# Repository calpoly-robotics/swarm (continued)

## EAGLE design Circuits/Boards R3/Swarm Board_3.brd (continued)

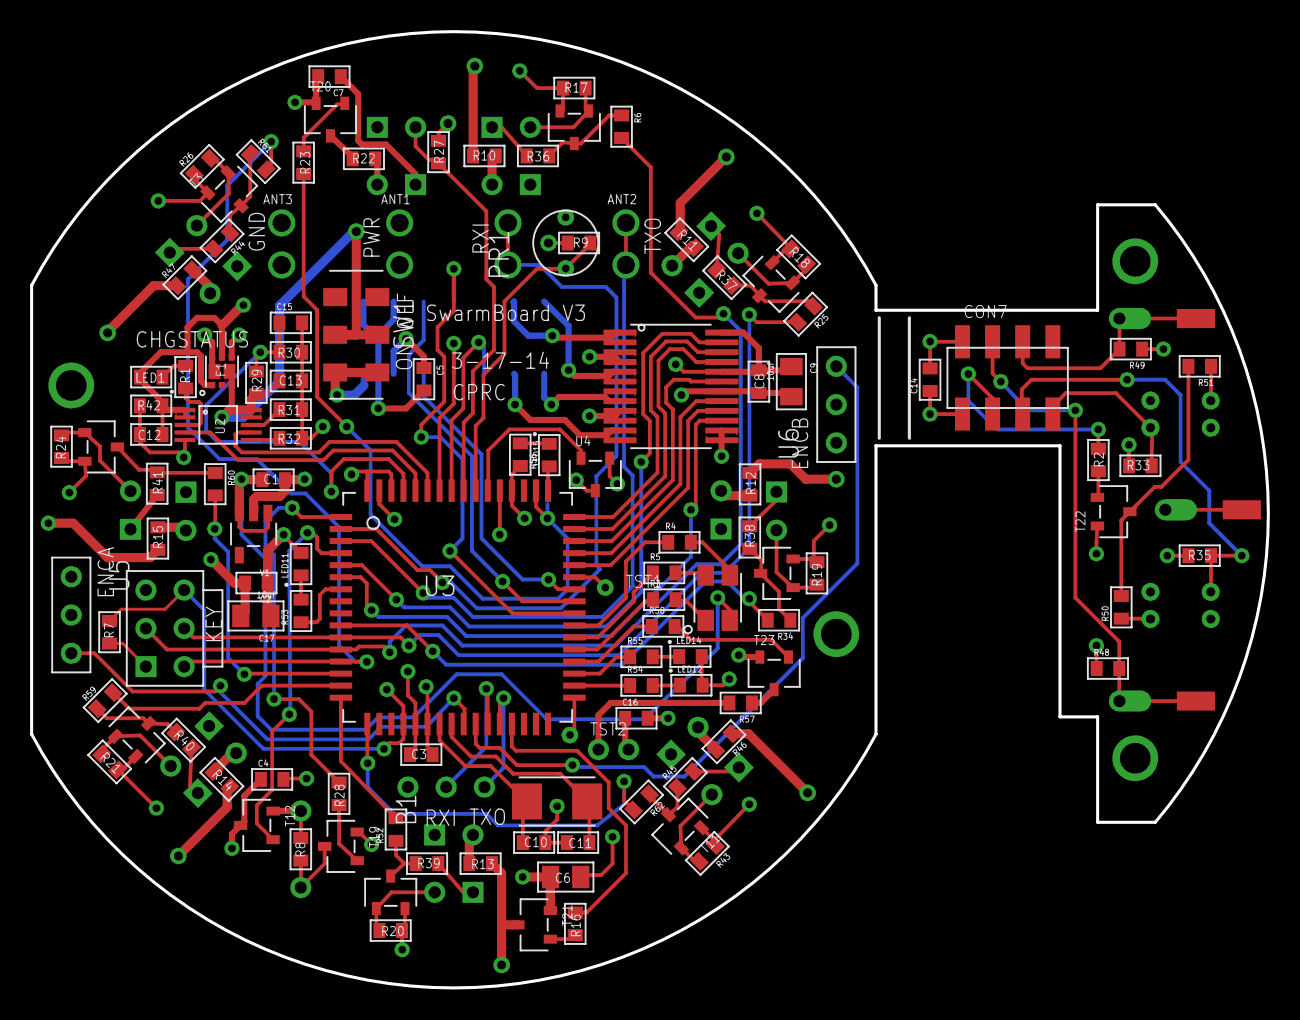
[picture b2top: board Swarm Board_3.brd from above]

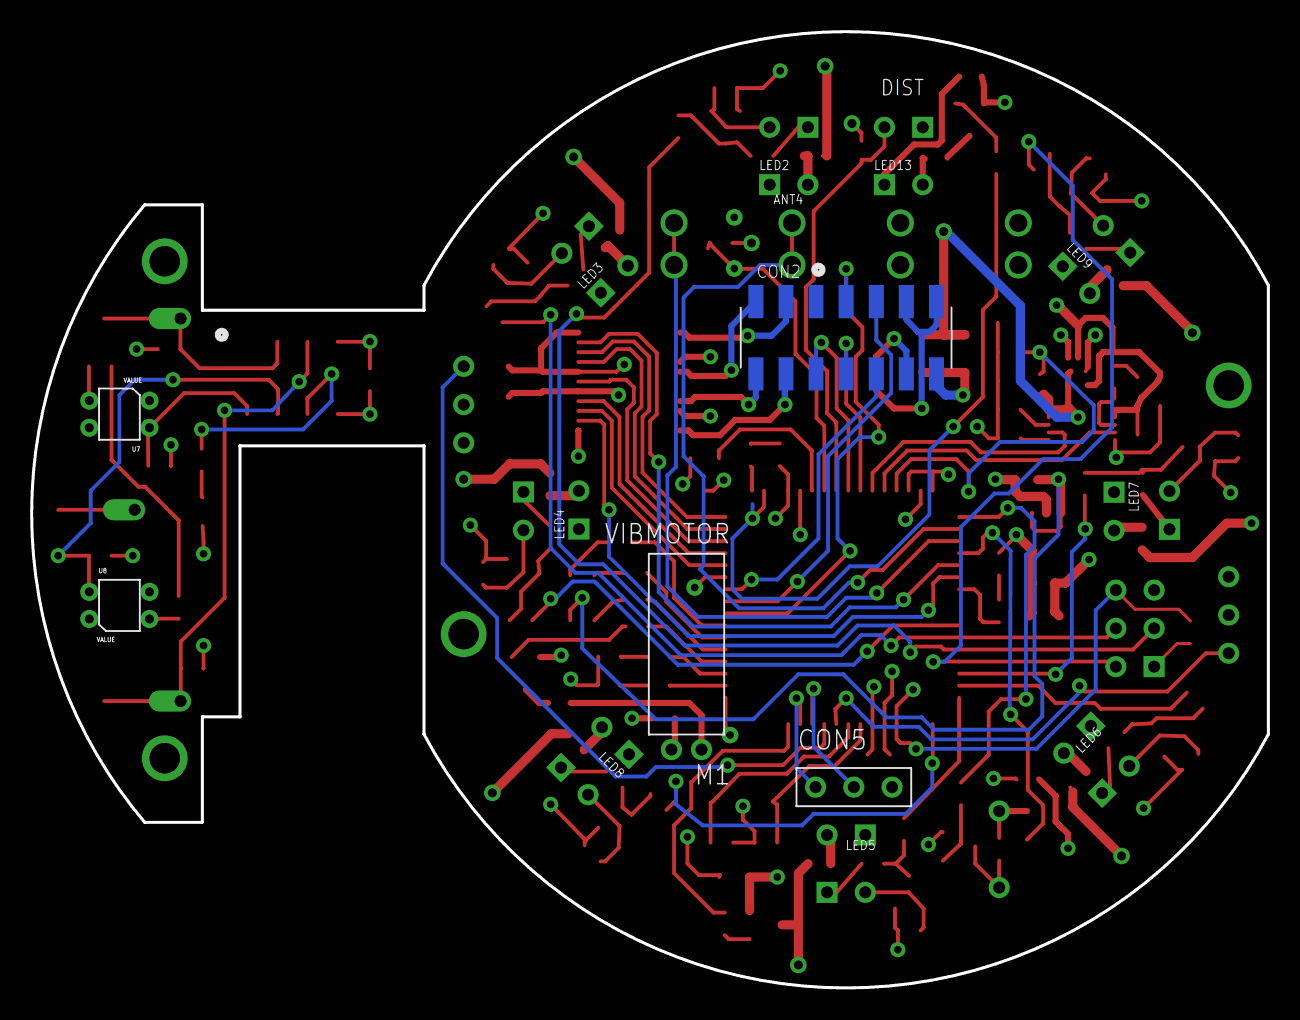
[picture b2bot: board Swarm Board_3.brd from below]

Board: 4 copper layers, 82.1 x 63.5 mm, 149 parts (14 on the bottom side), 116 nets.

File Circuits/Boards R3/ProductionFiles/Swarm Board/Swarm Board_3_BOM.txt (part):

Partlist exported from C:/Users/Jeffrey/Documents/GitHub/swarm/Circuits/Boards R3/Swarm Board_3.sch at 3/21/2014 3:27:04 AM

Qty Value             Device                Package                   Parts                                                                                                      Description                                        
1   0                 RES0603               0603                      R57                                                                                                                                                           
1   1.5k              RES0603               0603                      R1                                                                                                                                                            
8   100               RES0603               0603                      R10, R11, R12, R13, R14, R15, R46, R47                                                                                                                        
2   100k              RES0603               0603                      R29, R30                                                                                                                                                      
22  10k               RES0603               0603                      R6, R7, R17, R18, R19, R20, R21, R24, R25, R26, R27, R31, R34, R42, R43, R48, R49, R52, R59, R60, R61, R62                                                    
3   10uf              CAP0805               0805                      C6, C9, C17                                                                                                                                                   
2   12pf              CAP0603               0603                      C10, C11                                                                                                                                                      
10  1k                RES0603               0603                      R2, R8, R16, R23, R28, R53, R54, R55, R56, R58                                                                                                                
10  1uf               CAP0603               0603                      C1, C2, C3, C4, C5, C7, C8, C14, C15, C16                                                                                                                     
1   20k               RES0603               0603                      R9                                                                                                                                                            
3   220               RES0603               0603                      R3, R50, R51                                                                                                                                                  
2   22k               RES0603               0603                      R33, R35                                                                                                                                                      
1   2k                RES0603               0603                      R32                                                                                                                                                           
1   30                RES0603               0603                      R22                                                                                                                                                           
8   4.7k              RES0603               0603                      R36, R37, R38, R39, R40, R41, R44, R45                                                                                                                        
2   4.7uf             CAP0603               0603                      C12, C13                                                                                                                                                      
1   500k-20k          CDSPHOTORESISTOR      CDSPHOTOCELL              PR1                                                                                                        Digikey Part Number: PDV-P8103-ND                  
2   75                RES0603               0603                      R4, R5                                                                                                                                                        
1   8Mhz              NX5032GA-10.000000MHZ SMDXTAL                   XTAL1                                                                                                      Digikey Part Number: 644-1033-1-ND                 
2   AH182             AH182                 3PINHEADER_.100"          U5, U6                                                                                                     Digikey Part Number: AH182-PL-ADICT-ND             
4   ANTENNA           ANTENNA               ANTENNA                   ANT1, ANT2, ANT3, ANT4                                                                                                                                        
1   ATMEGA1281        ATMEGA1281            TQFP64                    U3                                                                                                         Digikey Part Number: ATMEGA1281V-8AU-ND            
1   CL-SB-22A         CL-SB-22A             CL-SB-22A-01T             SW1                                                                                                        Digikey Part Number: 563-1338-1-ND                 
1   FDFMA2P857        FDFMA2P857            MICROFET2X2MM             F1                                                                                                         Digikey Part Number: FDFMA2P857CT-ND               
2   GREEN             LED0603               LED0603                   LED14, LED15                                                                                                                                                  
1   HEADER_3X1        HEADER_3X1            3PINHEADER_.100"          CON5                                                                                                                                                          
9   IR                LED5MMRA              5MM_LED_RA                LED2, LED3, LED4, LED5, LED6, LED7, LED8, LED9, LED13                                                                                                         
5   IRLML6244TR       IRLML6244TR           SOT23                     T19, T20, T21, T22, T23                                                                                    Digikey Part Number: IRLML6244TRPBFCT-ND           
1   ISP(2X3)          ISP(2X3)              PINHEADER(2X3)            CON1                                                                                                                                                          
1   MAIN_CONNECTOR_14 MAIN_CONNECTOR_14     FEMALE_HEADER_2MM_2X7_SMD CON2                                                                                                       Digikey Part Number: H10965-ND                     
1   MAIN_CONNECTOR_8  MAIN_CONNECTOR_8      FEMALE_HEADER_2MM_2X4     CON7                                                                                                       Digikey Part Number: H10962-ND                     
1   MCP73833          MCP73833              MSOP10                    U2                                                                                                         Manufacturer Part Number: MCP73833-AMI/UN          
1   MCP9700A          MCP9700A              SOT23                     U4                                                                                                         Digikey Part Number: MCP9700AT-E/TTCT-ND           
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
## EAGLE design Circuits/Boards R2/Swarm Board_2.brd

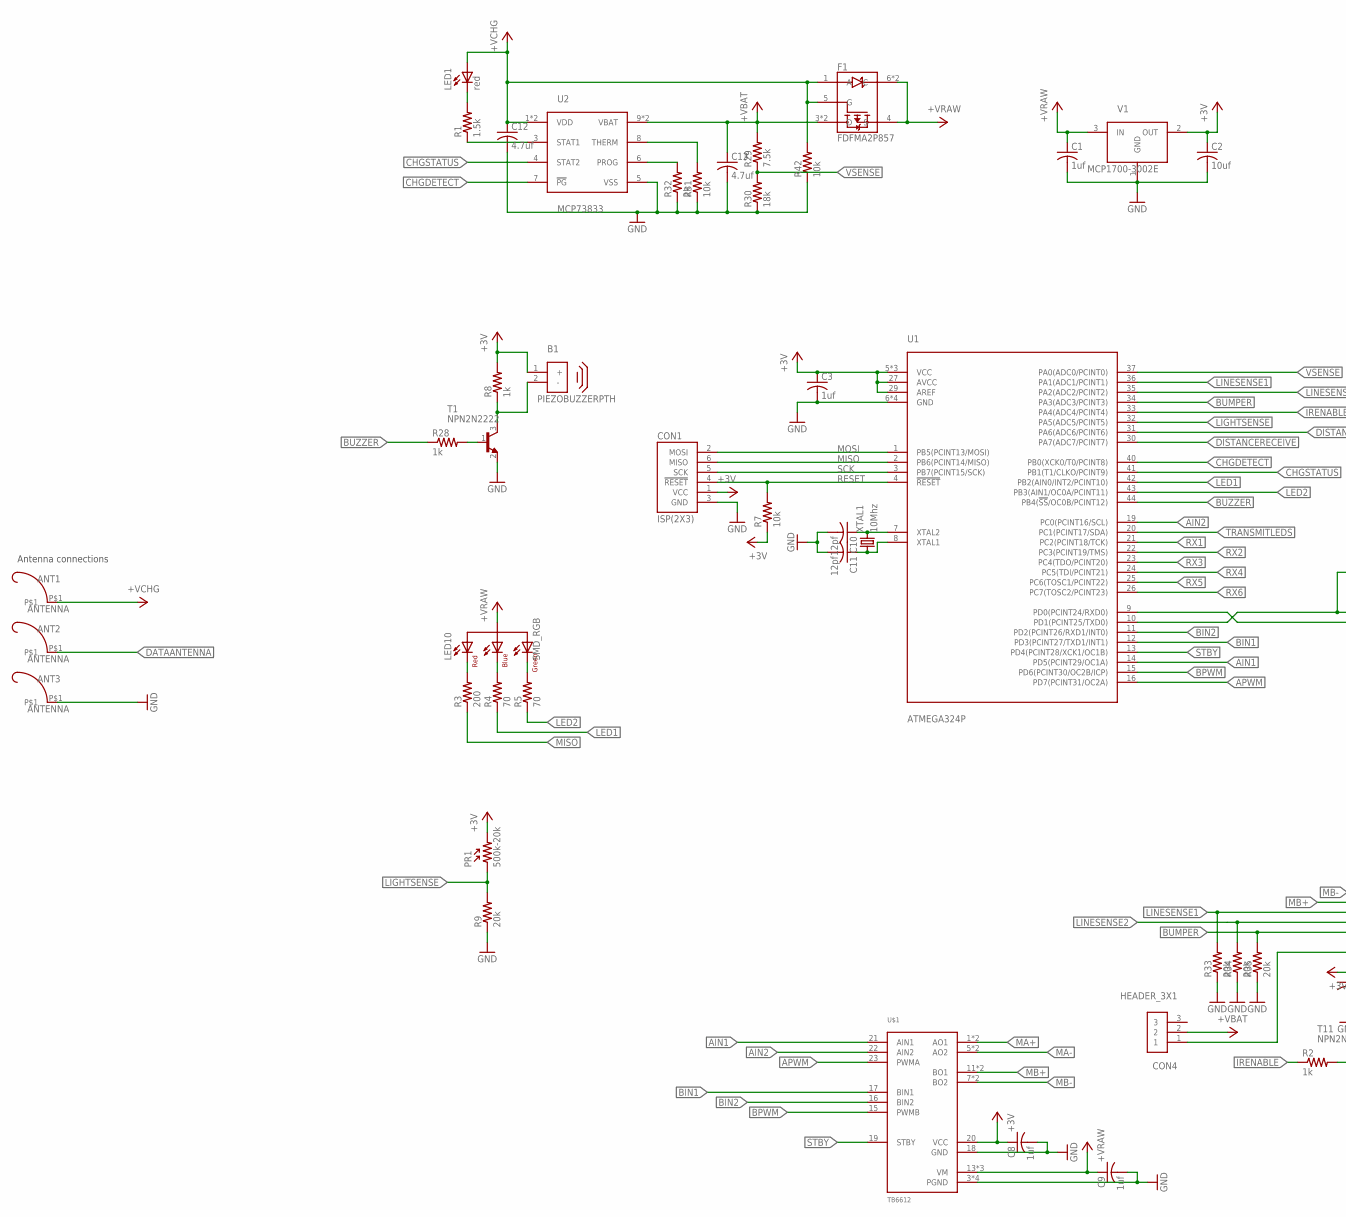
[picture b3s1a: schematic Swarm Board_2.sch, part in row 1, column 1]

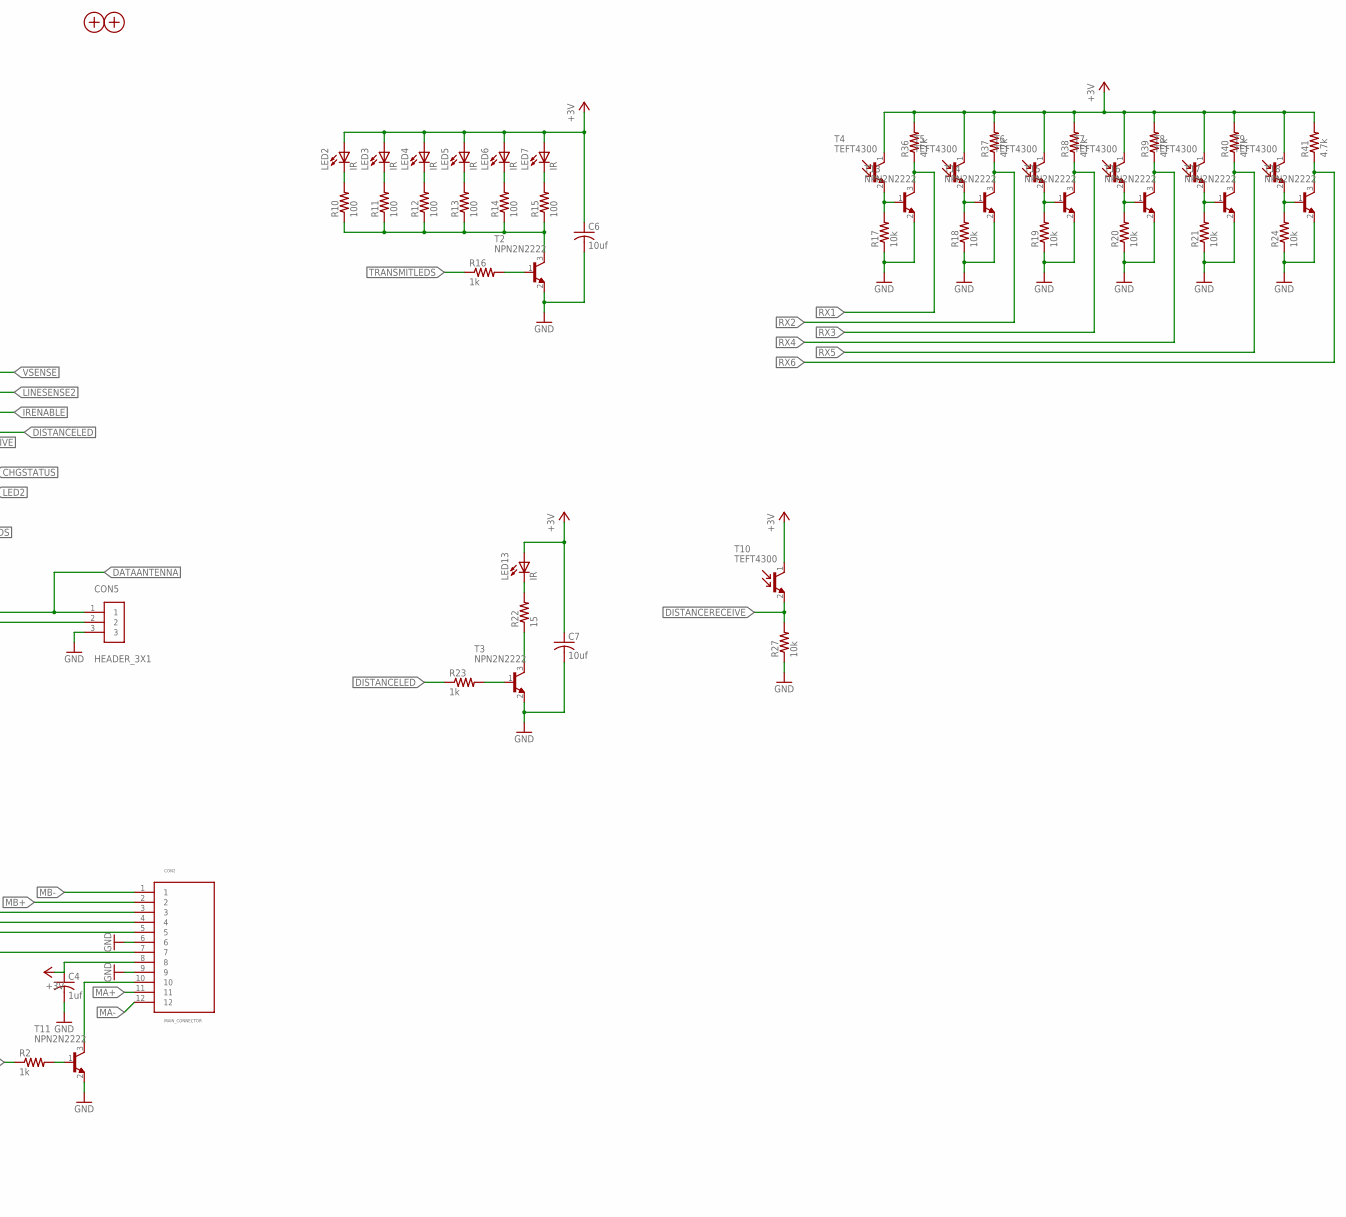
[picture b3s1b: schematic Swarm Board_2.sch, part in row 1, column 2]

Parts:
ANT1, ANT2, ANT3: ANTENNA
B1: PIEZOBUZZERPTH; PIEZOBUZZER
C1, C3, C4, C8, C9: 1uf; 0603
C2, C6, C7: 10uf; 0805
C10, C11: 12pf; 0603
C12, C13: 4.7uf; 0603
CON1: ISP(2X3); PINHEADER(2X3)
CON2: MAIN_CONNECTOR; FEMALE_HEADER_2MM_2X6
CON4, CON5: HEADER_3X1; 3PINHEADER_.100"
F1: FDFMA2P857; MICROFET2X2MM
H1, H2: MOUNTINGHOLE
LED1: red; LED0603
LED2, LED3, LED4, LED5, LED6, LED7, LED13: IR; 5MM_LED_RA
LED10: SMD_RGB; PLCC4
PR1: 500k-20k; CDSPHOTOCELL
R1: 1.5k; 0603
R2, R8, R16, R23, R28: 1k; 0603
R3: 200; 0603
R4, R5: 70; 0603
R7, R17, R18, R19, R20, R21, R24, R27, R31, R42: 10k; 0603
R9, R33, R34, R35: 20k; 0603
R10, R11, R12, R13, R14, R15: 100; 0603
R22: 15; 0603
R29: 7.5k; 0603
R30: 18k; 0603
R32: 2k; 0603
R36, R37, R38, R39, R40, R41: 4.7k; 0603
T1, T2, T3, T11, T13, T14, T15, T16, T17, T18: NPN2N2222; SOT23
T4, T5, T6, T7, T8, T9, T10: TEFT4300; 3MM_LED_RA
U1: ATMEGA324P; TQFP44
U2: MCP73833; MSOP10
U$1: TB6612; 24SSOP
V1: MCP1700-3002E; (TT/NB)SOT-23(3PAD)
XTAL1: 10Mhz; SMDXTAL

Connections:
+3V: B1.1 (+), C2.1, C3.1, C4.1, C6.1, C7.1, C8.1, CON1.1 (VCC), CON2.8, LED2.1 (A), LED3.1 (A), LED4.1 (A), LED5.1 (A), LED6.1 (A), LED7.1 (A), LED13.1 (A), PR1.2, R7.1, R8.2, R36.2, R37.2, R38.2, R39.2, R40.2, R41.2, T4.1 (C), T5.1 (C), T6.1 (C), T7.1 (C), T8.1 (C), T9.1 (C), T10.1 (C), U1.5 (VCC), U1.17 (VCC), U1.27 (AVCC), U1.29 (AREF), U1.38 (VCC), U$1.20 (VCC), V1.2 (OUT)
+VBAT: C13.1, CON4.2, F1.3 (D), F1.8 (D), R29.2, U2.9 (VBAT), U2.10 (VBAT)
+VCHG: ANT1.P$1, C12.1, F1.1 (A), F1.5 (G), LED1.2 (A), R42.2, U2.1 (VDD), U2.2 (VDD)
+VRAW: C1.1, C9.1, F1.4 (S), F1.6 (C), F1.7 (C), LED10.2 (COMMONANODE), U$1.13 (VM), U$1.14 (VM), U$1.24 (VM), V1.3 (IN)
AIN1: U1.14 (PD5(PCINT29/OC1A)), U$1.21 (AIN1)
AIN2: U1.19 (PC0(PCINT16/SCL)), U$1.22 (AIN2)
APWM: U1.16 (PD7(PCINT31/OC2A)), U$1.23 (PWMA)
BIN1: U1.12 (PD3(PCINT27/TXD1/INT1)), U$1.17 (BIN1)
BIN2: U1.11 (PD2(PCINT26/RXD1/INT0)), U$1.16 (BIN2)
BPWM: U1.15 (PD6(PCINT30/OC2B/ICP)), U$1.15 (PWMB)
BUMPER: CON2.5, R35.2, U1.34 (PA3(ADC3/PCINT3))
BUZZER: R28.1, U1.44 (PB4(!SS!/OC0B/PCINT12))
CHGDETECT: U1.40 (PB0(XCK0/T0/PCINT8)), U2.7 (!PG)
CHGSTATUS: U1.41 (PB1(T1/CLKO/PCINT9)), U2.4 (STAT2)
DATAANTENNA: ANT2.P$1, CON5.1, U1.10 (PD1(PCINT25/TXD0))
DISTANCELED: R23.1, U1.31 (PA6(ADC6/PCINT6))
DISTANCERECEIVE: R27.2, T10.2 (E), U1.30 (PA7(ADC7/PCINT7))
GND: ANT3.P$1, C1.2, C2.2, C3.2, C4.2, C6.2, C7.2, C8.2, C9.2, C10.2, C11.2, C12.2, C13.2, CON1.3 (GND), CON2.6, CON2.9, CON5.3, R9.1, R17.1, R18.1, R19.1, R20.1, R21.1, R24.1, R27.1, R30.1, R31.1, R32.1, R33.1, R34.1, R35.1, R42.1, T1.2 (E), T2.2 (E), T3.2 (E), T11.2 (E), T13.2 (E), T14.2 (E), T15.2 (E), T16.2 (E), T17.2 (E), T18.2 (E), U1.6 (GND), U1.18 (GND), U1.28 (GND), U1.39 (GND), U2.5 (VSS), U$1.3 (PGND), U$1.4 (PGND), U$1.9 (PGND), U$1.10 (PGND), U$1.18 (GND), V1.1 (GND)
IRENABLE: R2.1, U1.33 (PA4(ADC4/PCINT4))
LED1: R4.1, U1.42 (PB2(AIN0/INT2/PCINT10))
LED2: R5.1, U1.43 (PB3(AIN1/OC0A/PCINT11))
LIGHTSENSE: PR1.1, R9.2, U1.32 (PA5(ADC5/PCINT5))
LINESENSE1: CON2.3, R33.2, U1.36 (PA1(ADC1/PCINT1))
LINESENSE2: CON2.4, R34.2, U1.35 (PA2(ADC2/PCINT2))
MA+: CON2.11, U$1.1 (AO1), U$1.2 (AO1)
MA-: CON2.12, U$1.5 (AO2), U$1.6 (AO2)
MB+: CON2.2, U$1.11 (BO1), U$1.12 (BO1)
MB-: CON2.1, U$1.7 (BO2), U$1.8 (BO2)
MISO: CON1.6 (MISO), R3.1, U1.2 (PB6(PCINT14/MISO))
MOSI: CON1.2 (MOSI), U1.1 (PB5(PCINT13/MOSI))
unnamed: LED1.1 (C), R1.2
unnamed: R2.2, T11.1 (B)
unnamed: CON2.10, T11.3 (C)
unnamed: CON5.2, U1.9 (PD0(PCINT24/RXD0))
unnamed: B1.2 (-), R8.1, T1.3 (C)
unnamed: R10.1, R11.1, R12.1, R13.1, R14.1, R15.1, T2.3 (C)
unnamed: R16.2, T2.1 (B)
unnamed: R22.1, T3.3 (C)
unnamed: LED2.2 (C), R10.2
unnamed: LED3.2 (C), R11.2
unnamed: LED4.2 (C), R12.2
unnamed: LED5.2 (C), R13.2
unnamed: LED6.2 (C), R14.2
unnamed: LED7.2 (C), R15.2
unnamed: R23.2, T3.1 (B)
unnamed: R31.2, U2.8 (THERM)
unnamed: C10.1, U1.7 (XTAL2), XTAL1.2
unnamed: C11.1, U1.8 (XTAL1), XTAL1.1
unnamed: LED13.2 (C), R22.2
unnamed: R28.2, T1.1 (B)
unnamed: R17.2, T4.2 (E), T13.1 (B)
unnamed: R32.2, U2.6 (PROG)
unnamed: CON2.7, CON4.1
unnamed: LED10.1 (REDCATHODE), R3.2
unnamed: LED10.3 (BLUECATHODE), R4.2
unnamed: LED10.4 (GREENCATHODE), R5.2
unnamed: R1.1, U2.3 (STAT1)
unnamed: R24.2, T9.2 (E), T18.1 (B)
unnamed: R21.2, T8.2 (E), T17.1 (B)
unnamed: R20.2, T7.2 (E), T16.1 (B)
unnamed: R19.2, T6.2 (E), T15.1 (B)
unnamed: R18.2, T5.2 (E), T14.1 (B)
RESET: CON1.4 (!RESET), R7.2, U1.4 (!RESET)
RX1: R36.1, T13.3 (C), U1.21 (PC2(PCINT18/TCK))
RX2: R37.1, T14.3 (C), U1.22 (PC3(PCINT19/TMS))
RX3: R38.1, T15.3 (C), U1.23 (PC4(TDO/PCINT20))
RX4: R39.1, T16.3 (C), U1.24 (PC5(TDI/PCINT21))
RX5: R40.1, T17.3 (C), U1.25 (PC6(TOSC1/PCINT22))
RX6: R41.1, T18.3 (C), U1.26 (PC7(TOSC2/PCINT23))
SCK: CON1.5 (SCK), U1.3 (PB7(PCINT15/SCK))
STBY: U1.13 (PD4(PCINT28/XCK1/OC1B)), U$1.19 (STBY)
TRANSMITLEDS: R16.1, U1.20 (PC1(PCINT17/SDA))
VSENSE: R29.1, R30.2, U1.37 (PA0(ADC0/PCINT0))

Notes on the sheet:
Antenna connections

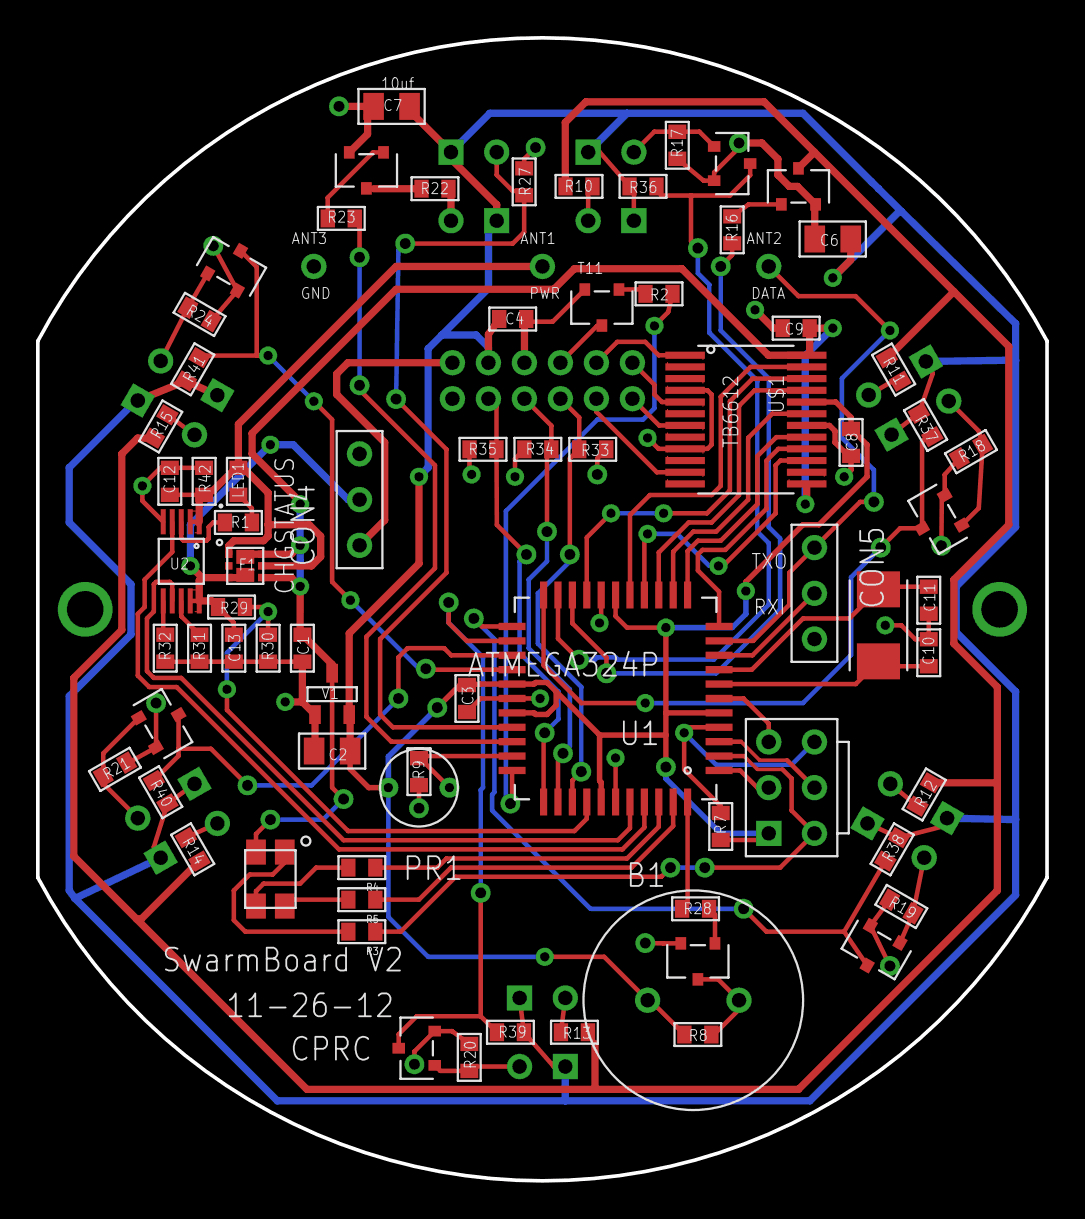
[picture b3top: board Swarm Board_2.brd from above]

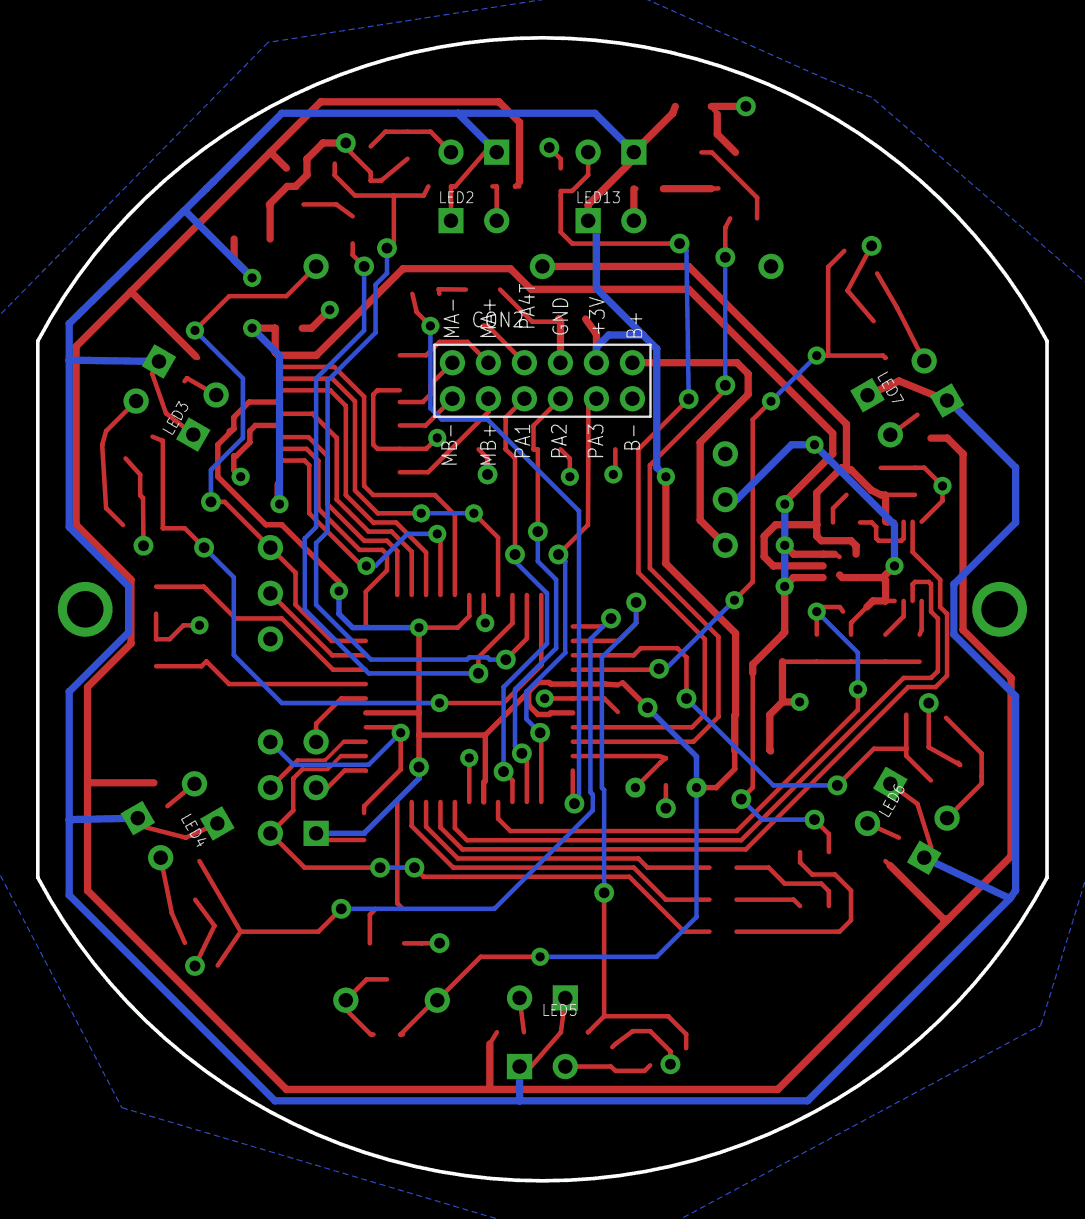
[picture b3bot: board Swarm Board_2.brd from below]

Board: 2 copper layers, 56.1 x 63.5 mm, 94 parts (8 on the bottom side), 73 nets.

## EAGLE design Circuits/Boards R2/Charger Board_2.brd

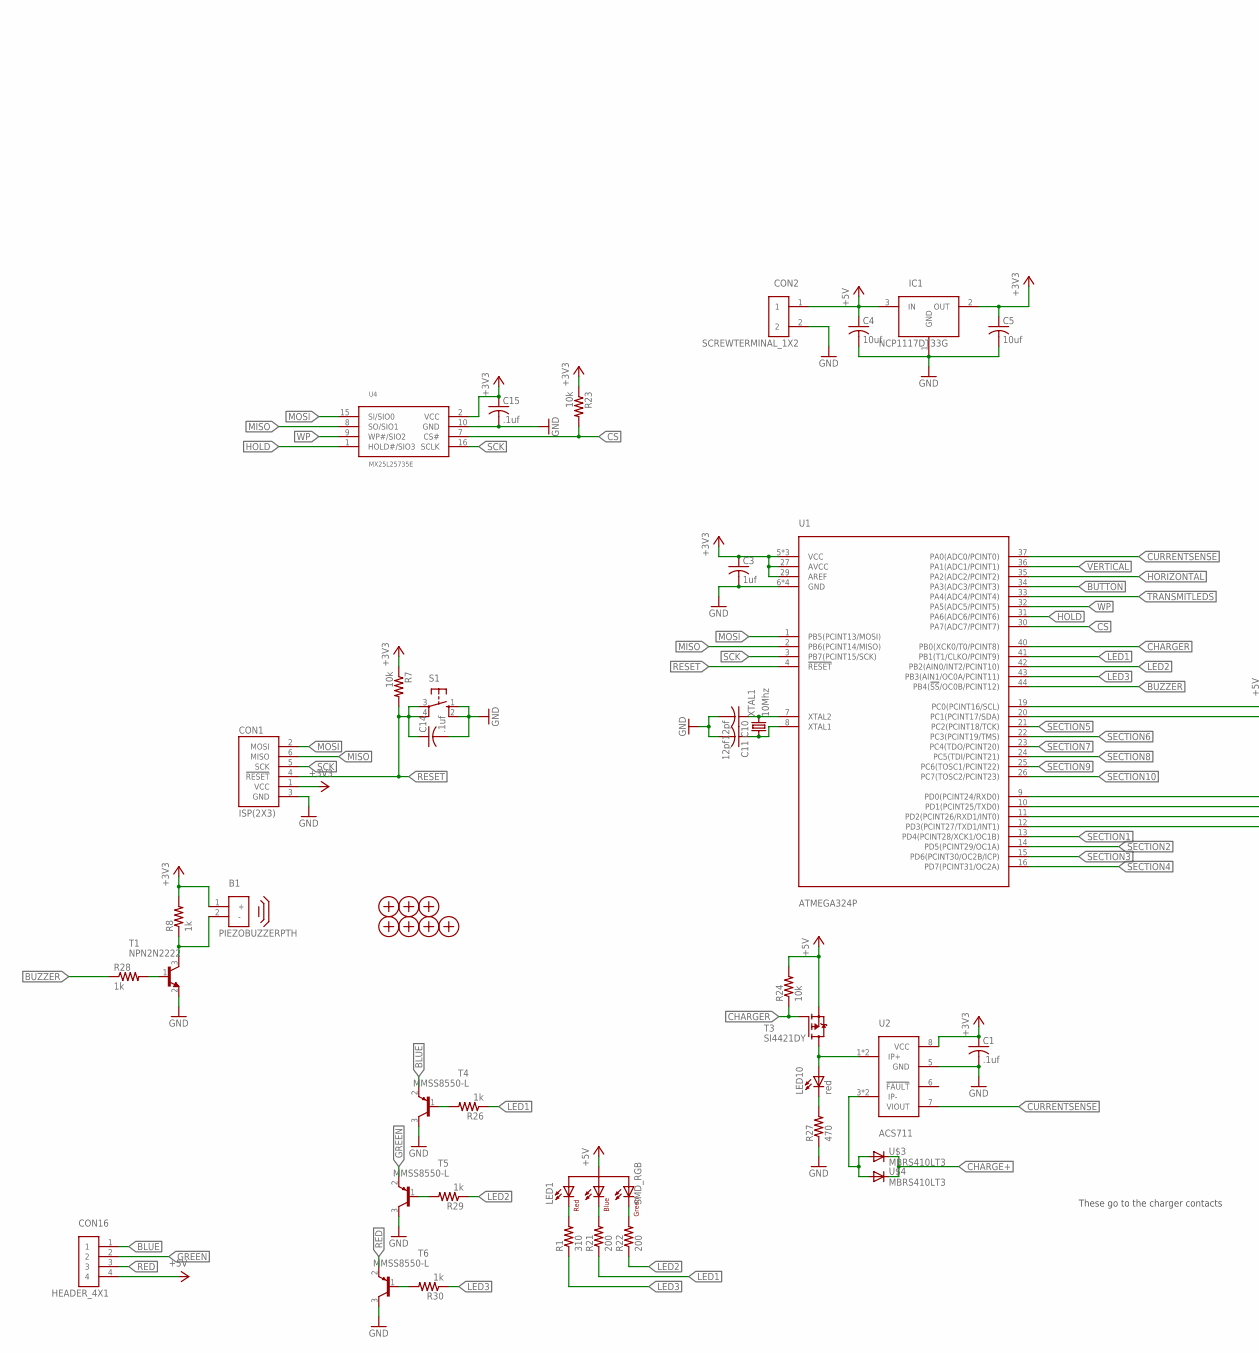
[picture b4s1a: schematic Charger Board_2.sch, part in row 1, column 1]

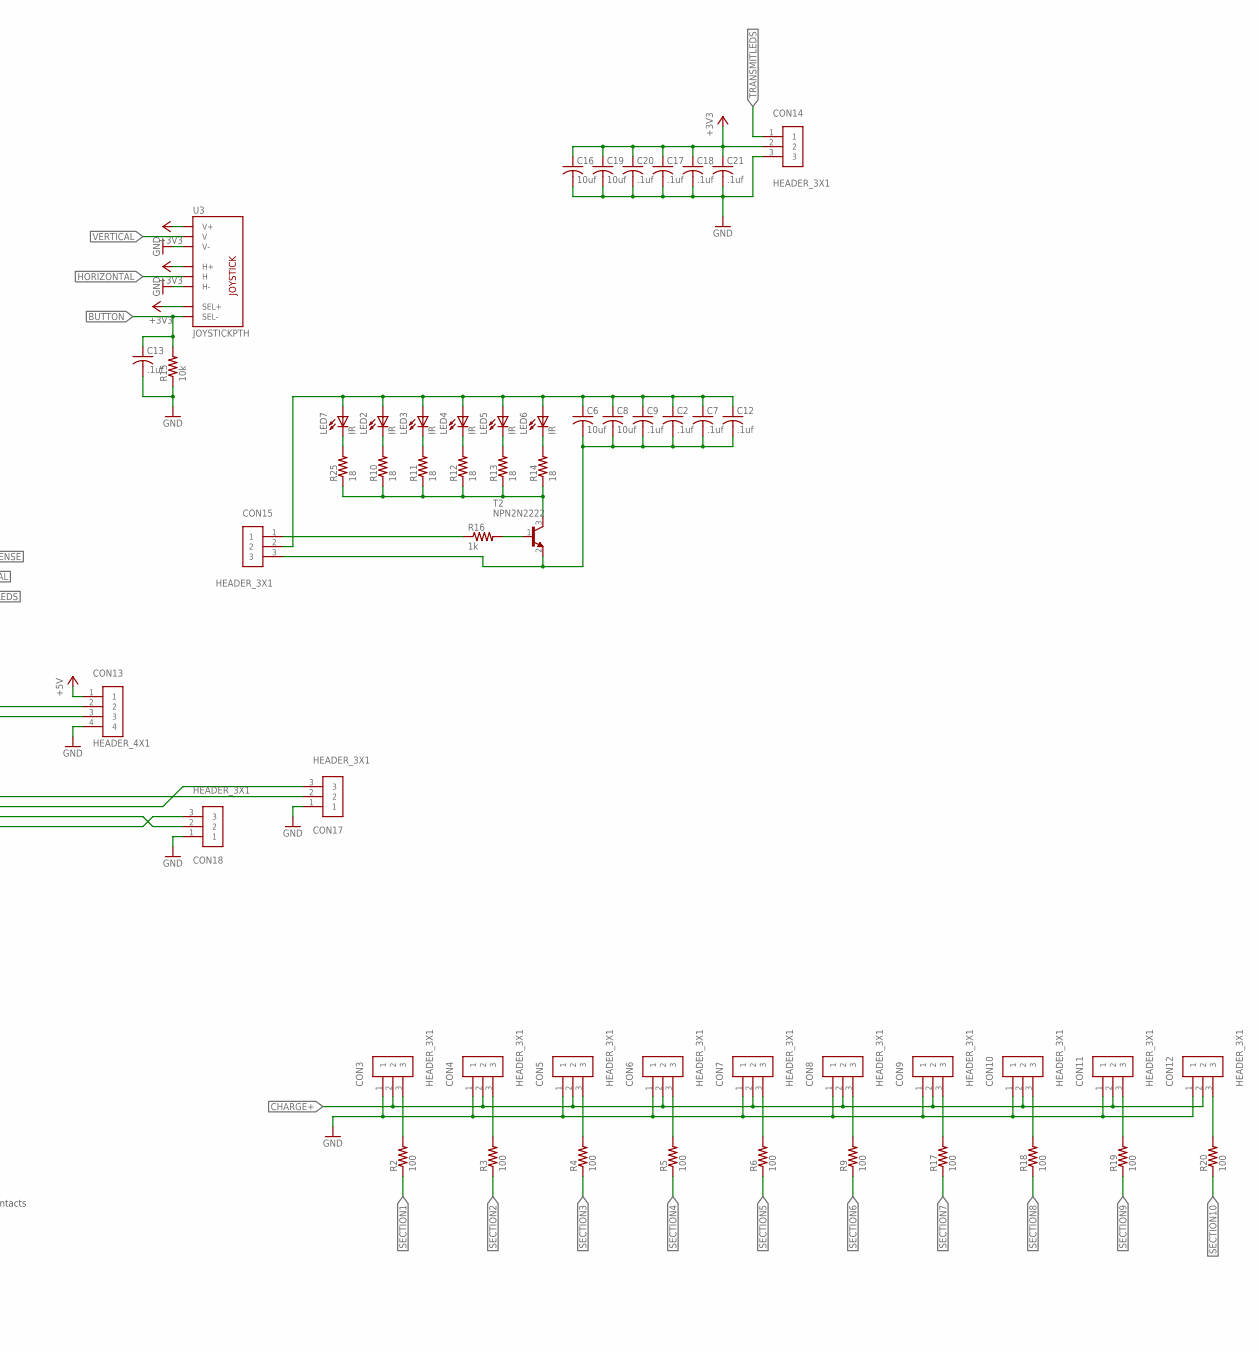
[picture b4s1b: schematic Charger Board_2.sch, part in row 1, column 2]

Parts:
B1: PIEZOBUZZERPTH; PIEZOBUZZER
C1, C2, C7, C9, C12, C13, C14, C15, C17, C18, C20, C21: .1uf; 0603
C3: 1uf; 0603
C4, C5, C6, C8, C16, C19: 10uf; 0805
C10, C11: 12pf; 0603
CON1: ISP(2X3); PINHEADER(2X3)
CON2: SCREWTERMINAL_1X2
CON3, CON4, CON5, CON6, CON7, CON8, CON9, CON10, CON11, CON12, CON14, CON15, CON17, CON18: HEADER_3X1; 3PINHEADER_.100"
CON13, CON16: HEADER_4X1; 4PINHEADER_.100"
H1, H2, H3, H4, H5, H6, H7: MOUNTINGHOLE
IC1: NCP1117DT33G; DPAK
LED1: SMD_RGB; PLCC4
LED2, LED3, LED4, LED5, LED6, LED7: IR; 5MM_LED_RA
LED10: red; LED0603
R1: 310; 0603
R2, R3, R4, R5, R6, R9, R17, R18, R19, R20: 100; 0603
R7, R15, R23, R24: 10k; 0603
R8, R16, R26, R28, R29, R30: 1k; 0603
R10, R11, R12, R13, R14, R25: 18; 0603
R21, R22: 200; 0603
R27: 470; 0603
S1: 10-XX; B3F-10XX
T1, T2: NPN2N2222; SOT23
T3: SI4421DY; S0-8
T4, T5, T6: MMSS8550-L; SOT23
U1: ATMEGA324P; TQFP44
U2: ACS711; 8SOIC
U3: JOYSTICKPTH; JOYSTICK
U4: MX25L25735E; SOIC16R
U$3, U$4: MBRS410LT3; SMD_DIODE
XTAL1: 10Mhz; SMDXTAL

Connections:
+3V3: B1.1 (+), C1.1, C3.1, C5.1, C15.1, C16.1, C17.1, C18.1, C19.1, C20.1, C21.1, CON1.1 (VCC), CON14.2, IC1.2 (OUT), R7.1, R8.2, R23.1, U1.5 (VCC), U1.17 (VCC), U1.27 (AVCC), U1.29 (AREF), U1.38 (VCC), U2.8 (VCC), U3.B1A (SEL+), U3.H1 (H+), U3.V1 (V+), U4.2 (VCC)
+5V: C4.1, CON2.1, CON13.1, CON16.4, IC1.3 (IN), LED1.2 (COMMONANODE), R24.2, T3.1 (S), T3.2 (S), T3.3 (S)
BLUE: CON16.1, T4.2 (E)
BUTTON: C13.1, R15.2, U1.34 (PA3(ADC3/PCINT3)), U3.B2A (SEL-)
BUZZER: R28.1, U1.44 (PB4(!SS!/OC0B/PCINT12))
CHARGE+: CON3.2, CON4.2, CON5.2, CON6.2, CON7.2, CON8.2, CON9.2, CON10.2, CON11.2, CON12.2, U$3.2 (C), U$4.2 (C)
CHARGER: R24.1, T3.4 (G), U1.40 (PB0(XCK0/T0/PCINT8))
CS: R23.2, U1.30 (PA7(ADC7/PCINT7)), U4.7 (CS#)
CURRENTSENSE: U1.37 (PA0(ADC0/PCINT0)), U2.7 (VIOUT)
GND: C1.2, C3.2, C4.2, C5.2, C10.2, C11.2, C13.2, C14.2, C15.2, C16.2, C17.2, C18.2, C19.2, C20.2, C21.2, CON1.3 (GND), CON2.2, CON3.1, CON4.1, CON5.1, CON6.1, CON7.1, CON8.1, CON9.1, CON10.1, CON11.1, CON12.1, CON13.4, CON14.3, CON17.1, CON18.1, IC1.1 (GND), R15.1, R27.1, S1.1 (S), S1.2 (S1), T1.2 (E), T4.3 (C), T5.3 (C), T6.3 (C), U1.6 (GND), U1.18 (GND), U1.28 (GND), U1.39 (GND), U2.5 (GND), U3.H3 (H-), U3.V3 (V-), U4.10 (GND)
GREEN: CON16.2, T5.2 (E)
HOLD: U1.31 (PA6(ADC6/PCINT6)), U4.1 (HOLD#/SIO3)
HORIZONTAL: U1.35 (PA2(ADC2/PCINT2)), U3.H2 (H)
LED1: R21.1, R26.1, U1.41 (PB1(T1/CLKO/PCINT9))
LED2: R22.1, R29.1, U1.42 (PB2(AIN0/INT2/PCINT10))
LED3: R1.1, R30.1, U1.43 (PB3(AIN1/OC0A/PCINT11))
MISO: CON1.6 (MISO), U1.2 (PB6(PCINT14/MISO)), U4.8 (SO/SIO1)
MOSI: CON1.2 (MOSI), U1.1 (PB5(PCINT13/MOSI)), U4.15 (SI/SIO0)
unnamed: LED10.2 (A), T3.5 (D), T3.6 (D), T3.7 (D), T3.8 (D), U2.1 (IP+), U2.2 (IP+)
unnamed: CON15.1, R16.1
unnamed: C2.1, C6.1, C7.1, C8.1, C9.1, C12.1, CON15.2, LED2.1 (A), LED3.1 (A), LED4.1 (A), LED5.1 (A), LED6.1 (A), LED7.1 (A)
unnamed: CON18.2, U1.11 (PD2(PCINT26/RXD1/INT0))
unnamed: C2.2, C6.2, C7.2, C8.2, C9.2, C12.2, CON15.3, T2.2 (E)
unnamed: LED7.2 (C), R25.2
unnamed: CON17.3, U1.10 (PD1(PCINT25/TXD0))
unnamed: CON17.2, U1.9 (PD0(PCINT24/RXD0))
unnamed: B1.2 (-), R8.1, T1.3 (C)
unnamed: R10.1, R11.1, R12.1, R13.1, R14.1, R25.1, T2.3 (C)
unnamed: R16.2, T2.1 (B)
unnamed: C10.1, U1.7 (XTAL2), XTAL1.2
unnamed: LED2.2 (C), R10.2
unnamed: LED3.2 (C), R11.2
unnamed: LED4.2 (C), R12.2
unnamed: LED5.2 (C), R13.2
unnamed: LED6.2 (C), R14.2
unnamed: CON18.3, U1.12 (PD3(PCINT27/TXD1/INT1))
unnamed: LED10.1 (C), R27.2
unnamed: U2.3 (IP-), U2.4 (IP-), U$3.1 (A), U$4.1 (A)
unnamed: CON3.3, R2.2
unnamed: C11.1, U1.8 (XTAL1), XTAL1.1
unnamed: R28.2, T1.1 (B)
unnamed: CON4.3, R3.2
unnamed: CON5.3, R4.2
unnamed: CON6.3, R5.2
unnamed: CON7.3, R6.2
unnamed: CON8.3, R9.2
unnamed: CON9.3, R17.2
unnamed: CON10.3, R18.2
unnamed: CON11.3, R19.2
unnamed: CON12.3, R20.2
unnamed: R26.2, T4.1 (B)
unnamed: LED1.1 (REDCATHODE), R1.2
unnamed: LED1.3 (BLUECATHODE), R21.2
unnamed: LED1.4 (GREENCATHODE), R22.2
unnamed: R29.2, T5.1 (B)
unnamed: R30.2, T6.1 (B)
RED: CON16.3, T6.2 (E)
RESET: C14.1, CON1.4 (!RESET), R7.2, S1.3, S1.4 (P1), U1.4 (!RESET)
SCK: CON1.5 (SCK), U1.3 (PB7(PCINT15/SCK)), U4.16 (SCLK)
SCL: CON13.2, U1.19 (PC0(PCINT16/SCL))
SDA: CON13.3, U1.20 (PC1(PCINT17/SDA))
SECTION1: R2.1, U1.13 (PD4(PCINT28/XCK1/OC1B))
SECTION2: R3.1, U1.14 (PD5(PCINT29/OC1A))
SECTION3: R4.1, U1.15 (PD6(PCINT30/OC2B/ICP))
SECTION4: R5.1, U1.16 (PD7(PCINT31/OC2A))
SECTION5: R6.1, U1.21 (PC2(PCINT18/TCK))
SECTION6: R9.1, U1.22 (PC3(PCINT19/TMS))
SECTION7: R17.1, U1.23 (PC4(TDO/PCINT20))
SECTION8: R18.1, U1.24 (PC5(TDI/PCINT21))
SECTION9: R19.1, U1.25 (PC6(TOSC1/PCINT22))
SECTION10: R20.1, U1.26 (PC7(TOSC2/PCINT23))
TRANSMITLEDS: CON14.1, U1.33 (PA4(ADC4/PCINT4))
VERTICAL: U1.36 (PA1(ADC1/PCINT1)), U3.V2 (V)
WP: U1.32 (PA5(ADC5/PCINT5)), U4.9 (WP#/SIO2)

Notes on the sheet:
These go to the charger contacts
